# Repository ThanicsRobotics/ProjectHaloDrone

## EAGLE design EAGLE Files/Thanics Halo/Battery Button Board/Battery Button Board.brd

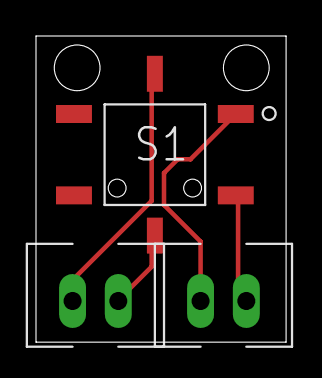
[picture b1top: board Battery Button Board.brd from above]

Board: 2 copper layers, 13.9 x 17.0 mm, 3 parts (0 on the bottom side), 4 nets.

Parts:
D1: XH_CONNECTOR
S1: SWITCH_CONNECTOR; XH_CONNECTOR
U$1: LED_TACT_SWITCH

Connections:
GND: D1.2, U$1.5
unnamed: D1.1, U$1.6
unnamed: S1.1, U$1.1
unnamed: S1.2, U$1.3

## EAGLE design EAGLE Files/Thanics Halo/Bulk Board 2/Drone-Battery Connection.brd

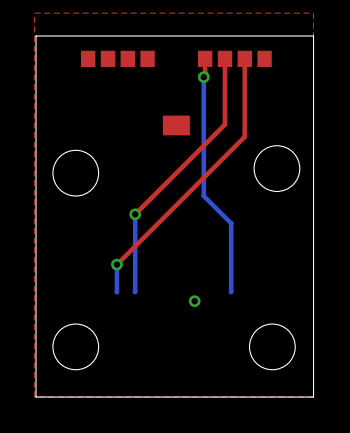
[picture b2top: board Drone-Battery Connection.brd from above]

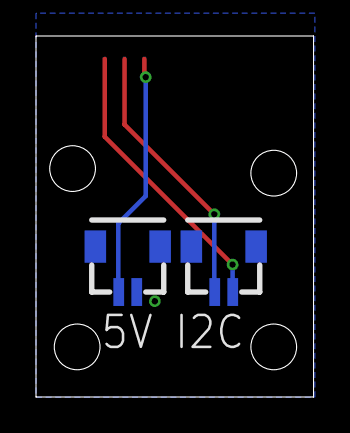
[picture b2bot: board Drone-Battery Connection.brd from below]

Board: 2 copper layers, 15.4 x 20.1 mm, 3 parts (2 on the bottom side), 4 nets.

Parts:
U$1: SPRING_BTB_8POS_MALE
U$2, U$3: JST_SH_2POS

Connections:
+5V: U$1.5, U$3.1
GND: U$1.8, U$3.2
SCL: U$1.7, U$2.2
SDA: U$1.6, U$2.1

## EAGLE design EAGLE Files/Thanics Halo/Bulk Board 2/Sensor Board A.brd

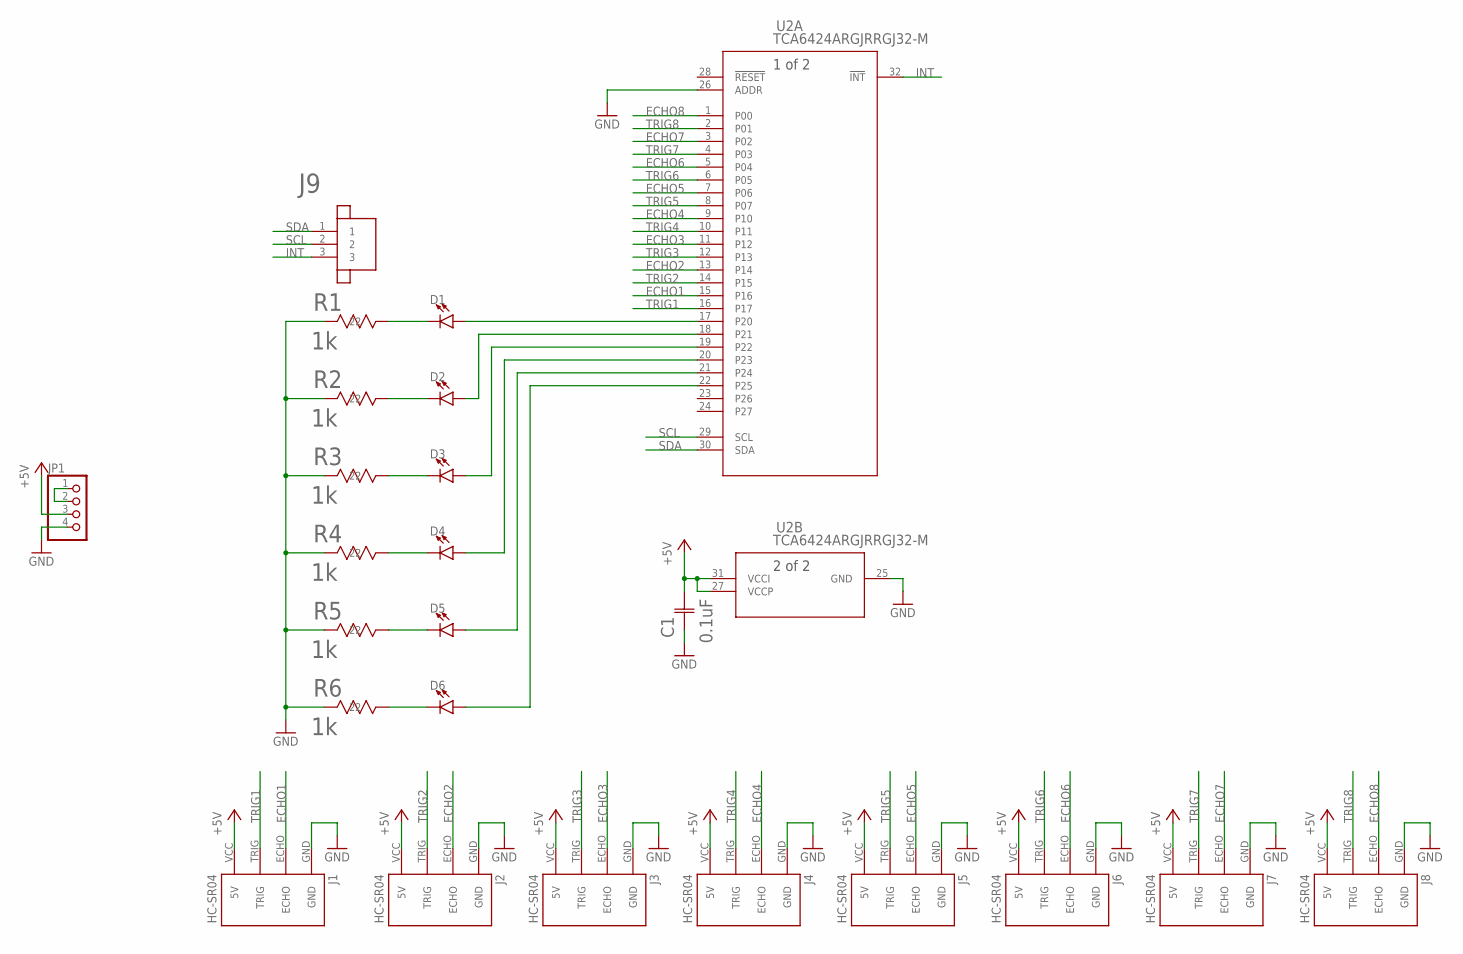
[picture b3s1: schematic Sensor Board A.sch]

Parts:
C1: 0.1uF; 0805
D1, D2, D3, D4, D5, D6: LED0603; LED-0603
J1, J2, J3, J4, J5, J6, J7, J8: HC-SR04; HC-SR04_FOOTPRINT
J9: JST_SH_3POS
JP1: PINHD-1X4; 1X04
R1, R2, R3, R4, R5, R6: 1k; RC0603N-M
U2: TCA6424ARGJRRGJ32-M; RGJ32-M

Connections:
+5V: C1.2, J1.VCC (5V), J2.VCC (5V), J3.VCC (5V), J4.VCC (5V), J5.VCC (5V), J6.VCC (5V), J7.VCC (5V), J8.VCC (5V), JP1.3, U2.27 (VCCP), U2.31 (VCCI)
ECHO1: J1.ECHO, U2.15 (P16)
ECHO2: J2.ECHO, U2.13 (P14)
ECHO3: J3.ECHO, U2.11 (P12)
ECHO4: J4.ECHO, U2.9 (P10)
ECHO5: J5.ECHO, U2.7 (P06)
ECHO6: J6.ECHO, U2.5 (P04)
ECHO7: J7.ECHO, U2.3 (P02)
ECHO8: J8.ECHO, U2.1 (P00)
GND: C1.1, J1.GND, J2.GND, J3.GND, J4.GND, J5.GND, J6.GND, J7.GND, J8.GND, JP1.4, R1.2 (22), R2.2 (22), R3.2 (22), R4.2 (22), R5.2 (22), R6.2 (22), U2.25 (GND), U2.26 (ADDR)
INT: J9.3, U2.32 (!INT)
unnamed: JP1.1, JP1.2
unnamed: D1.A, U2.17 (P20)
unnamed: D2.A, U2.18 (P21)
unnamed: D3.A, U2.19 (P22)
unnamed: D4.A, U2.20 (P23)
unnamed: D5.A, U2.21 (P24)
unnamed: D6.A, U2.22 (P25)
unnamed: D6.C, R6.1 (11)
unnamed: D5.C, R5.1 (11)
unnamed: D4.C, R4.1 (11)
unnamed: D3.C, R3.1 (11)
unnamed: D2.C, R2.1 (11)
unnamed: D1.C, R1.1 (11)
SCL: J9.2, U2.29 (SCL)
SDA: J9.1, U2.30 (SDA)
TRIG1: J1.TRIG, U2.16 (P17)
TRIG2: J2.TRIG, U2.14 (P15)
TRIG3: J3.TRIG, U2.12 (P13)
TRIG4: J4.TRIG, U2.10 (P11)
TRIG5: J5.TRIG, U2.8 (P07)
TRIG6: J6.TRIG, U2.6 (P05)
TRIG7: J7.TRIG, U2.4 (P03)
TRIG8: J8.TRIG, U2.2 (P01)

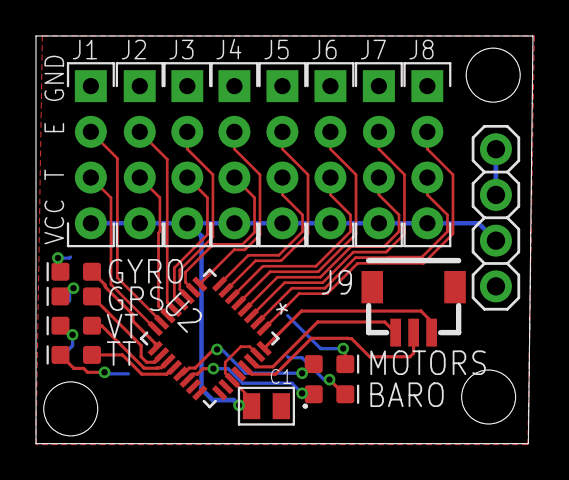
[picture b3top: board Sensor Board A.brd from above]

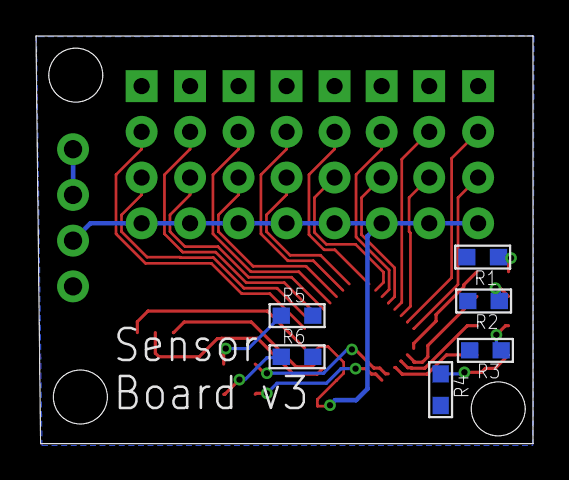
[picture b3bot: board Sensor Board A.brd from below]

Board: 2 copper layers, 27.6 x 22.6 mm, 24 parts (6 on the bottom side), 34 nets.

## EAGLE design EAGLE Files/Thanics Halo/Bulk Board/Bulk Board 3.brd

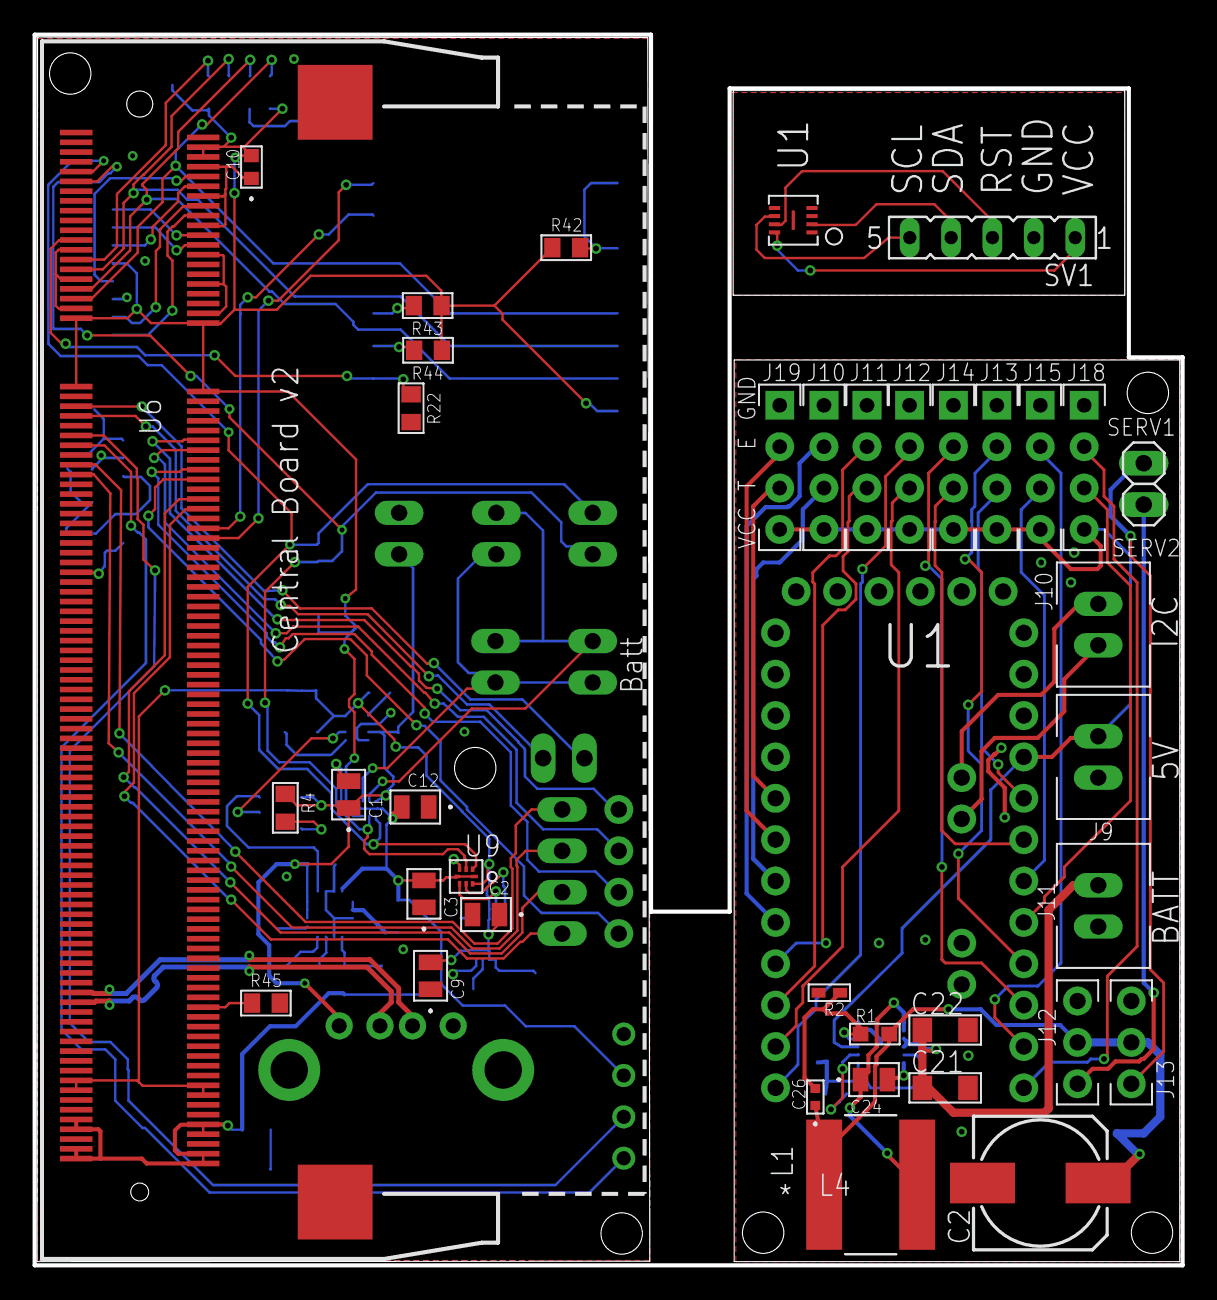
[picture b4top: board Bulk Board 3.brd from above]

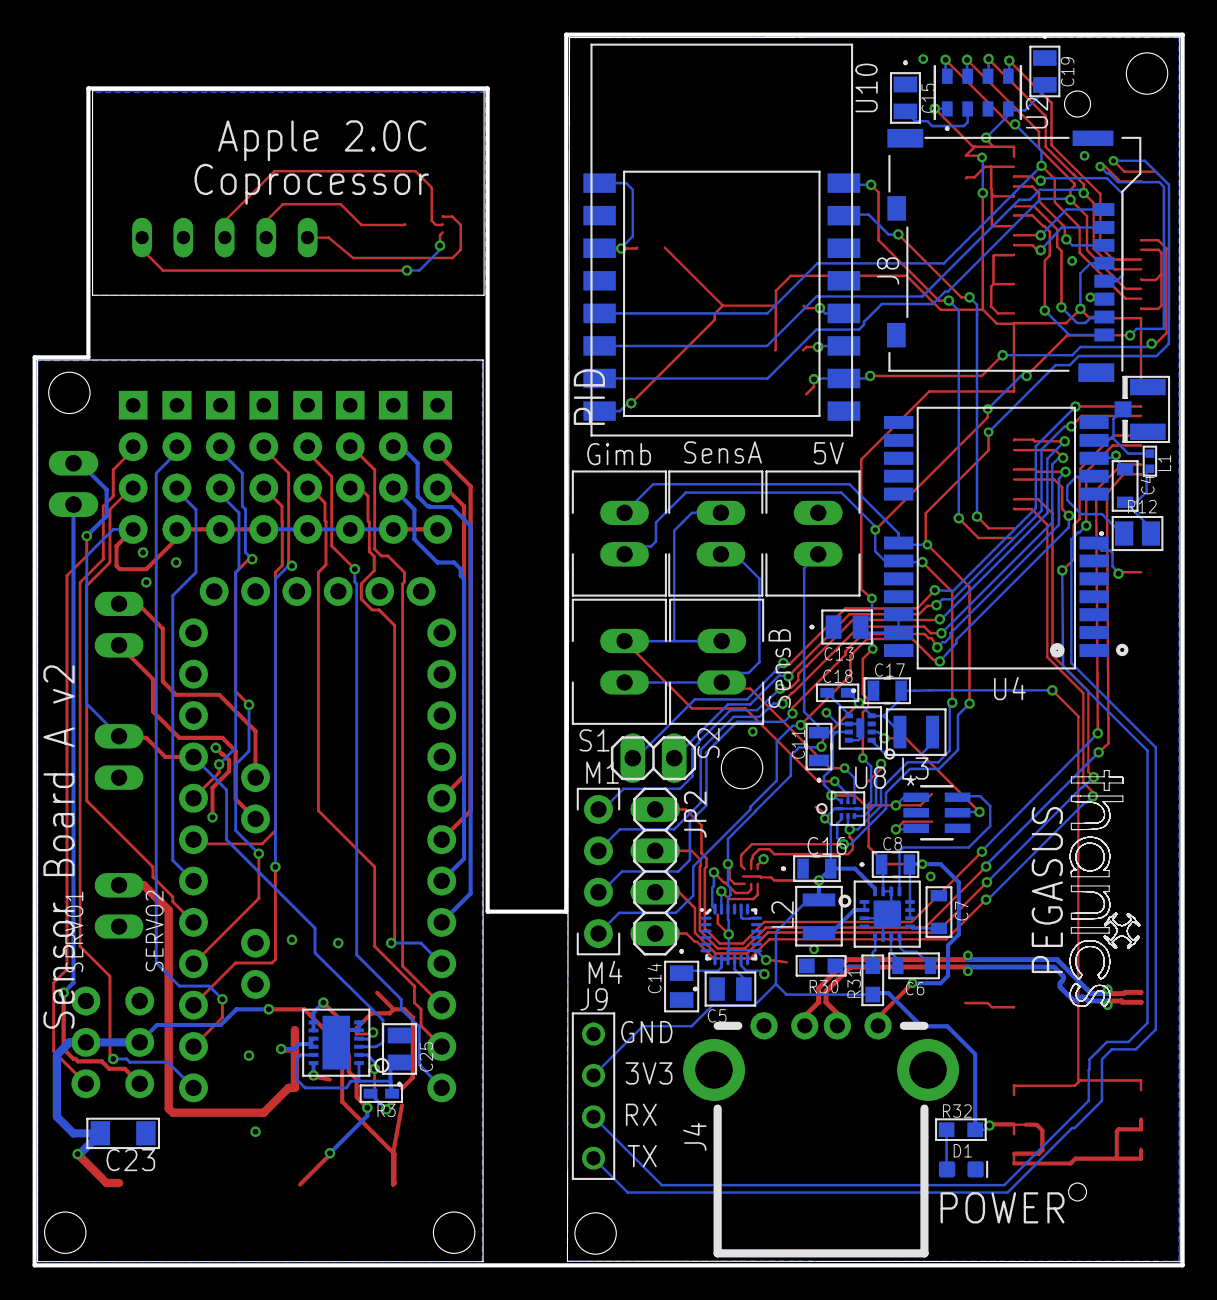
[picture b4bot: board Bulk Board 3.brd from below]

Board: 2 copper layers, 70.5 x 75.6 mm, 84 parts (45 on the bottom side), 91 nets.

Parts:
C1, C2, C3, C5, C9, C12, C13, C14, C24, C25: 0.1uF; 0805
C4: 10 nF; 0603_CAPACITOR
C6, C7: 10nF; 0603_CAPACITOR
C8, C11, C17: 10uF; G-21
C10: 2.2uF; G-188-M
C15, C19: 1uF; YAG_CC0805
C16: 22uF; G-21
C18: 560pF; CC0402N-M
C20: 100uF; 0810_POLCAP
C21, C22, C23: 10uF; 1206_MLCC
C26: 16pF; G-155-M
D1: GREEN; LED-0603
J1, J16: POWER_CONNECTOR; XH_CONNECTOR
J2, J3, J6, J7, J17: I2C_CONNECTOR; XH_CONNECTOR
J4: USB_A_RECEPT
J5: U.FL
J8: MICROSD
J9: 4_PIN_TELE_CONNECTOR
J10, J11, J12, J13, J14, J15, J18, J19: HC-SR04; HC-SR04_FOOTPRINT
J20, J21: SERVO_CONNECTOR
J22: GIMBAL_POWER_CONNECTOR; XH_CONNECTOR
JP1, JP3: 1X02
JP2: 1X04
L1: 27 nH; 0402_INDUCTOR
L2, L3: 470nH; 470NH_INDUCTOR
L4: 3.3uH; IND_BOURNS_SRN8040
R1, R31: 499k; RC0603N-M
R2, R3: 95.3k; RC0402N-M
R4, R22, R42, R43, R44, R45: 10k; RC0805N
R12: 10; STA_RNCP0805-M
R30: 160k; RC0603N-M
R32: 20R; RC0603N-M
SV1: FE05-1
U1: QFN40P300X300X105-25N
U2: LGA8-M
U3: LM3880MF-1AA/NOPBMF06A-M; MF06A-M
U4: NEO-M8
U5: TPS6209; VQFN16
U6: COMPUTE_MODULE; SO-DIMM
U7: MIC23050; MLF(ML)_8PIN
U8, U9: 8-UMLP
U10: ESP-12
U11: PRO-MINI-2
U$1: 12LD4X3DFN
U$2: APPLE_2.0C_COPROCESSOR; PG-USON-8-1
U$12: 4_PIN_CONNECTOR

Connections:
1.8V: C2.1, C9.2, C14.1, C17.2, C18.2, L3.P$2, U1.8, U1.9, U1.13, U1.22, U6.183, U6.184, U6.185, U6.186, U7.4, U9.8
+3V3: C3.2, C10.2, C12.2, C13.2, C16.2, C19.2, J8.4, J9.3, L2.P$2, R31.1, R32.2, R42.1, R43.1, R44.1, U2.1, U2.4, U4.22, U4.23, U5.16, U6.4, U6.6, U6.39, U6.40, U6.41, U6.42, U6.191, U6.192, U6.193, U6.194, U6.197, U6.198, U6.199, U6.200, U8.1, U8.5, U9.1, U9.5, U10.8
+5V: C1.1, C8.2, C11.2, J1.1, J4.1, R4.1, U3.1, U5.10, U5.11, U5.12, U7.7, U8.8
+5V1: J10.VCC, J11.VCC, J12.VCC, J13.VCC, J14.VCC, J15.VCC, J16.1, J18.VCC, J19.VCC, U11.VCC, U$1.3
ECHO1: J19.ECHO, U11.D3
ECHO2: J10.ECHO, U11.D5
ECHO3: J11.ECHO, U11.D7
ECHO4: J12.ECHO, U11.D9
ECHO5: J13.ECHO, U11.D13
ECHO6: J14.ECHO, U11.D12
ECHO7: J15.ECHO, U11.D11
ECHO8: J18.ECHO, U11.D10
GND: C1.2, C2.2, C3.1, C4.1, C5.1, C7.1, C8.1, C9.1, C10.1, C11.1, C12.1, C13.1, C14.2, C15.1, C16.1, C17.1, C19.1, D1.C, J1.2, J4.4, J4.5, J4.6, J5.P$1, J5.P$2, J8.6, J8.9, J8.10, J8.11, J8.12, J8.13, J9.4, R22.2, R30.2, R45.2, U1.11, U1.18, U1.20, U2.3, U3.2, U4.7, U4.10, U4.12, U4.13, U4.24, U5.3, U5.6, U5.14, U5.15, U5.17, U6.1, U6.7, U6.8, U6.13, U6.14, U6.19, U6.20, U6.25, U6.26, U6.31, U6.32, U6.37, U6.38, U6.43, U6.44, U6.49, U6.50, U6.55, U6.56, U6.61, U6.62, U6.67, U6.68, U6.73, U6.74, U6.79, U6.80, U6.85, U6.86, U6.91, U6.92, U6.97, U6.98, U6.103, U6.104, U6.109, U6.110, U6.115, U6.116, U6.121, U6.122, U6.127, U6.133, U6.134, U6.139, U6.140, U6.145, U6.146, U6.151, U6.152, U6.157, U6.163, U6.164, U6.169, U6.170, U6.181, U6.182, U6.187, U6.188, U6.195, U6.196, U6.G1, U6.G2, U7.6, U7.8, U7.EP, U8.4, U9.4, U10.9
GND1: C20.-, C21.P$2, C22.P$2, C23.P$1, C25.2, J10.GND, J11.GND, J12.GND, J13.GND, J14.GND, J15.GND, J16.2, J18.GND, J19.GND, J20.3, J21.3, J22.2, R2.2, U11.GND, U11.GND1, U$1.5, U$1.6, U$1.EP
GND2: SV1.2, U$2.1, U$2.9
I2C_SCL: J7.1, U4.19, U6.11, U8.3, U9.3
I2C_SCL_1V8: U1.23, U9.6
I2C_SCL_5V: J2.1, J3.1, J6.1, U8.6
I2C_SDA: J7.2, U4.18, U6.9, U8.2, U9.2
I2C_SDA_1V8: U1.24, U9.7
I2C_SDA_5V: J2.2, J3.2, J6.2, U8.7
LED1: JP2.1, U6.57
LED2: JP2.2, U6.59
LED3: JP2.3, U6.64
LED4: JP2.4, U6.66
MOTOR1: U6.52, U$12.1
MOTOR2: U6.54, U$12.2
MOTOR3: U6.58, U$12.3
MOTOR4: U6.60, U$12.4
unnamed: J5.P$3, L1.P$1, U4.11
unnamed: C6.2, U5.7
unnamed: C6.1, U5.8
unnamed: D1.A, R32.1
unnamed: U3.6, U5.13
unnamed: U3.5, U7.2
unnamed: C26.2, R1.1, R2.1, U$1.4
unnamed: C24.2, U$1.12
unnamed: C24.1, L4.2, U$1.7, U$1.8
unnamed: R3.2, U$1.2
unnamed: C5.2, U1.10
unnamed: C15.2, U2.2
unnamed: R12.1, U4.9
unnamed: C4.2, L1.P$2, R12.2
unnamed: C7.2, U5.9
unnamed: L2.P$1, U5.1, U5.2
unnamed: L3.P$1, U7.1
unnamed: R42.2, U10.1, U10.3
unnamed: R43.2, U10.12
unnamed: R30.1, R31.2, U5.5
unnamed: C18.1, U7.5
unnamed: R44.2, U10.11
unnamed: R45.1, U6.168
POWER_SEQ_EN: R4.2, U3.3
RST: SV1.3, U$2.7
SCL: J17.1, U11.A5
SCL1: SV1.5, U$2.6
SDA: J17.2, U11.A4
SDA1: SV1.4, U$2.2
SDX_CLK: J8.5, U6.10
SDX_CMD: J8.3, U6.12
SDX_D0: J8.7, U6.16
SDX_D1: J8.8, U6.18
SDX_D2: J8.1, U6.22
SDX_D3: J8.2, U6.24
SERVO1: JP1.1, U6.45
SERVO2: JP1.2, U6.47
SERVO3: J21.1, JP3.2
SERVO4: J20.1, JP3.1
SPI_CS0: U2.5, U6.27
SPI_CS1: R22.1, U6.23, U10.10
SPI_MISO: U2.6, U6.29, U10.6
SPI_MOSI: U2.7, U6.33, U10.7
SPI_SCLK: U2.8, U6.35, U10.5
TRIG1: J19.TRIG, U11.D2
TRIG2: J10.TRIG, U11.D4
TRIG3: J11.TRIG, U11.D6
TRIG4: J12.TRIG, U11.D8
TRIG5: J13.TRIG, U11.A0
TRIG6: J14.TRIG, U11.A1
TRIG7: J15.TRIG, U11.A2
TRIG8: J18.TRIG, U11.A3
UART2_RX: U6.72, U10.16
UART2_TX: U6.70, U10.15
UART_RX: J9.1, U6.53
UART_TX: J9.2, U6.51
USB_D_N: J4.2, U6.167
USB_D_P: J4.3, U6.165
VCC: SV1.1, U$2.8
VDD: C25.1, R3.1, U$1.1, U$1.11
VOUT: C20.+, C23.P$2, C26.1, J20.2, J21.2, L4.1, R1.2
V_BATT: C21.P$1, C22.P$1, J22.1, U$1.9, U$1.10

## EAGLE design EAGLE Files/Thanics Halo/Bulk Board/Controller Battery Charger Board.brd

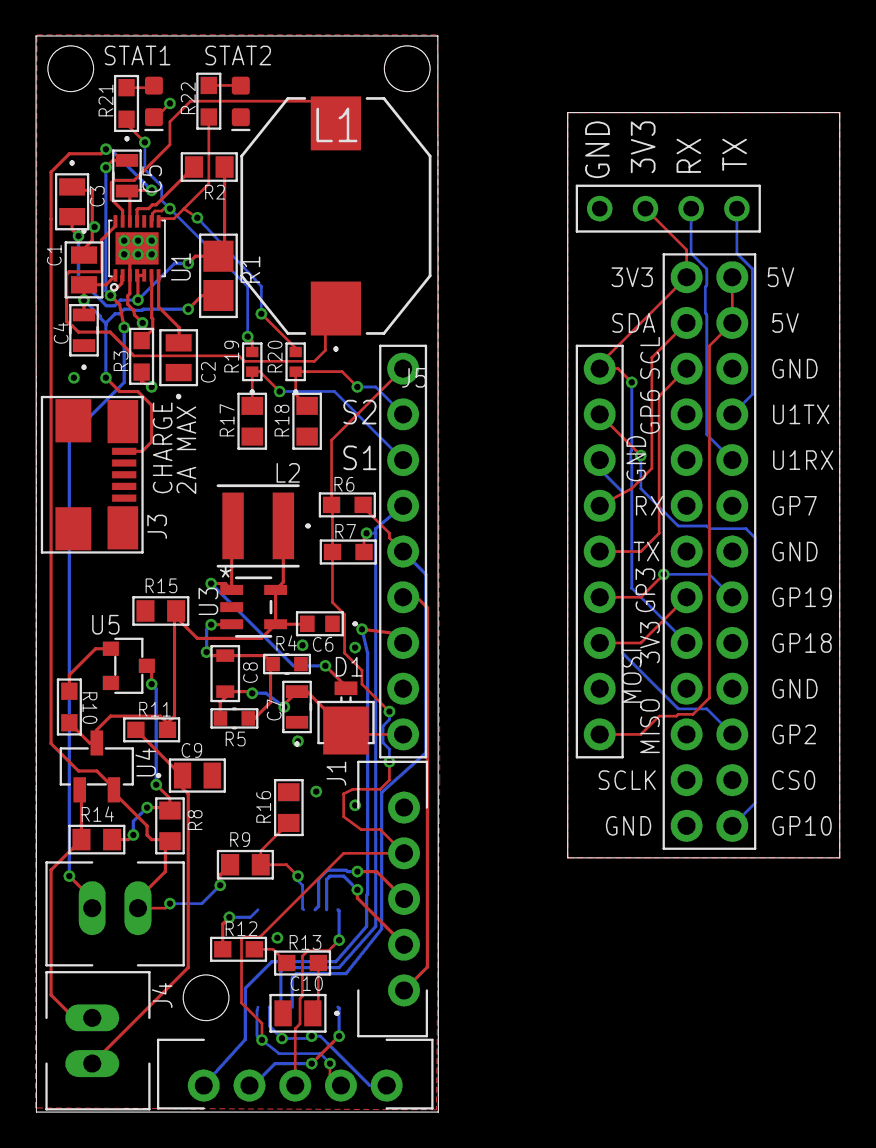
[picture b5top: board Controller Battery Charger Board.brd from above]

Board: 2 copper layers, 22.4 x 59.8 mm, 51 parts (1 on the bottom side), 48 nets.

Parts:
C1, C2, C10: 0.1uF; 0805
C3, C9: 1uF; YAG_CC0805
C4, C7: 10uF; G-21
C5: 22uF; G-21
C6: 2.2uF; G-188-M
C8: 470pF; 0603_CAPACITOR
D1: UPS5817_SCHOTTKY_DIODE; UPS5817_DIODE
D2: GREEN; LED-0603
D3: RED; LED-0603
J1, J2: JOYSTICK; JST-XH_5POS
J3: USB_MICRO_B_SMT
J4: 2_PIN_CONNECTOR; XH_CONNECTOR
J5, J7: RPI-AUX_BOARD_CONNECTOR; 9_PIN_CONNECTOR
J6: POWER_CONNECTOR; XH_CONNECTOR
L1: 4.7 uH; IND_BOURNS_SRR1005
L2: 10uH; IND_TAIYO_NR4018
R1: 100; 1206
R2, R8, R9, R14, R15, R16, R17, R18: 10k; RC0805N
R3, R10: 100k; RC0603N-M
R4: 13.3k; RC0603N
R5: 43k; RC0603N
R6, R7, R12, R13, R21, R22: 1k; RC0603N-M
R11: 1M; RC0603N-M
R19, R20: 5k; 0402
U1: AAT3620_BATT_CHARGER; AAT3620_TDFN
U2: 8 CH; 21-0055H_16-M
U3: LM27313XMF/NOPB; MF05A
U4: DMP3030SN_MOSFET; SC59_MOSFET
U5: SOT-23_(TO-236AB)
U$1: ORANGE_PI_ADAPTER1; ORANGE_PI_ADAPTER
U$3: 4_PIN_TELE_CONNECTOR

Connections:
+3V3: J1.2, J2.2, J5.9, R6.1, R7.1, U2.16
+5V: C7.2, C8.2, D1.C, J5.1, R5.2
GND: C1.1, C2.1, C3.1, C4.1, C6.1, C7.1, C9.2, C10.2, D2.C, D3.C, J1.1, J2.1, J3.5, J3.P$1, J3.P$2, J3.P$3, J3.P$4, J5.2, R3.1, R4.2, R15.1, R16.2, R17.1, R18.1, U1.3, U1.EP, U2.15, U3.2, U5.S
GNDA: J7.2, U$1.P$6, U$1.P$9, U$1.P$14, U$1.P$20, U$1.P$25, U$3.4
unnamed: J4.1, R14.1, U4.G
unnamed: C2.2, U1.7
unnamed: R3.2, U1.6
unnamed: L1.2, U1.13
unnamed: L1.1, U1.14
unnamed: C3.2, R1.1, R2.1, U1.4, U1.5
unnamed: C5.2, J6.1, R8.2, R9.1, U1.12, U4.S
unnamed: C8.1, R4.1, R5.1, U3.3
unnamed: J5.7, R17.2, R19.1
unnamed: J5.8, R18.2, R20.1
unnamed: R2.2, U1.11
unnamed: D1.A, L2.2, U3.1
unnamed: J7.1, U$1.P$2, U$1.P$4
unnamed: J5.6, R7.2, U2.14
unnamed: J1.5, J5.4
unnamed: R12.1, U2.1
unnamed: J1.3, U2.6
unnamed: J1.4, U2.7
unnamed: J2.3, U2.8
unnamed: J2.4, U2.9
unnamed: J5.5, R6.2, U2.13
unnamed: J2.5, J5.3
unnamed: C6.2, L2.1, R10.2, R11.2, R15.2, U3.4, U3.5, U4.D
unnamed: R12.2, R13.1
unnamed: R10.1, U5.G
unnamed: C9.1, J4.2, R11.1
unnamed: R8.1, R14.2, U5.D
unnamed: C10.1, R13.2
unnamed: J7.8, U$1.P$26
unnamed: J7.7, U$1.P$22
unnamed: J7.6, U$1.P$3
unnamed: J7.5, U$1.P$5
unnamed: C5.1, J6.2, U1.2
unnamed: J7.4, U$1.P$16
unnamed: J7.3, U$1.P$15
unnamed: U$1.P$8, U$3.1
unnamed: U$1.P$10, U$3.2
unnamed: R9.2, R16.1, U2.5
unnamed: R20.2, R22.1, U1.8
unnamed: J7.9, U$1.P$1, U$1.P$17, U$3.3
unnamed: D2.A, R21.2
unnamed: D3.A, R22.2
unnamed: R19.2, R21.1, U1.9
USB_5V: C1.2, C4.2, J3.1, R1.2, U1.1

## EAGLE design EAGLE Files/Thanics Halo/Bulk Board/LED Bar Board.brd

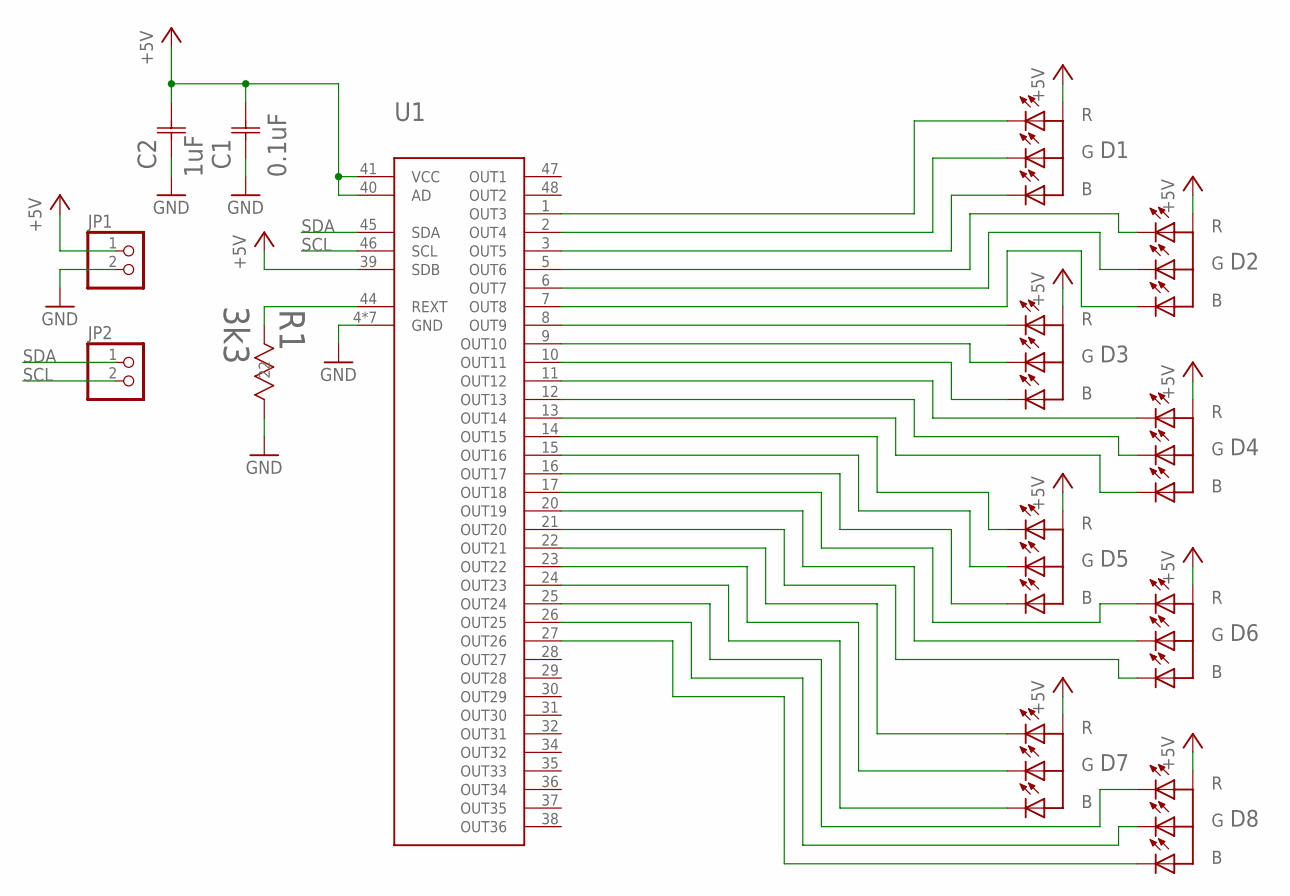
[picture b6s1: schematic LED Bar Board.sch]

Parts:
C1: 0.1uF; 0805
C2: 1uF; YAG_CC0805
D1, D2, D3, D4, D5, D6, D7, D8: ASMB-MTB0-0A3A2; ASMB-MTB0_LED
JP1, JP2: PINHD-1X2; 1X02
R1: 3k3; RC1206N-M
U1: IS31FL3236; TQFP-48

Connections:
+5V: C1.2, C2.2 (22), D1.1 (A), D2.1 (A), D3.1 (A), D4.1 (A), D5.1 (A), D6.1 (A), D7.1 (A), D8.1 (A), JP1.1, U1.39 (SDB), U1.40 (AD), U1.41 (VCC)
GND: C1.1, C2.1 (11), JP1.2, R1.1 (11), U1.4 (GND), U1.18 (GND), U1.19 (GND), U1.33 (GND), U1.42 (GND), U1.43 (GND), U1.EP (GND)
unnamed: D1.4 (R), U1.1 (OUT3)
unnamed: D1.3 (G), U1.2 (OUT4)
unnamed: D2.3 (G), U1.6 (OUT7)
unnamed: D1.2 (B), U1.3 (OUT5)
unnamed: D2.4 (R), U1.5 (OUT6)
unnamed: R1.2 (22), U1.44 (REXT)
unnamed: D3.4 (R), U1.8 (OUT9)
unnamed: D3.3 (G), U1.9 (OUT10)
unnamed: D3.2 (B), U1.10 (OUT11)
unnamed: D4.4 (R), U1.11 (OUT12)
unnamed: D4.3 (G), U1.12 (OUT13)
unnamed: D4.2 (B), U1.13 (OUT14)
unnamed: D5.4 (R), U1.14 (OUT15)
unnamed: D5.3 (G), U1.15 (OUT16)
unnamed: D5.2 (B), U1.16 (OUT17)
unnamed: D6.4 (R), U1.17 (OUT18)
unnamed: D6.3 (G), U1.20 (OUT19)
unnamed: D6.2 (B), U1.21 (OUT20)
unnamed: D7.4 (R), U1.22 (OUT21)
unnamed: D7.3 (G), U1.23 (OUT22)
unnamed: D7.2 (B), U1.24 (OUT23)
unnamed: D8.4 (R), U1.25 (OUT24)
unnamed: D8.3 (G), U1.26 (OUT25)
unnamed: D8.2 (B), U1.27 (OUT26)
unnamed: D2.2 (B), U1.7 (OUT8)
SCL: JP2.2, U1.46 (SCL)
SDA: JP2.1, U1.45 (SDA)

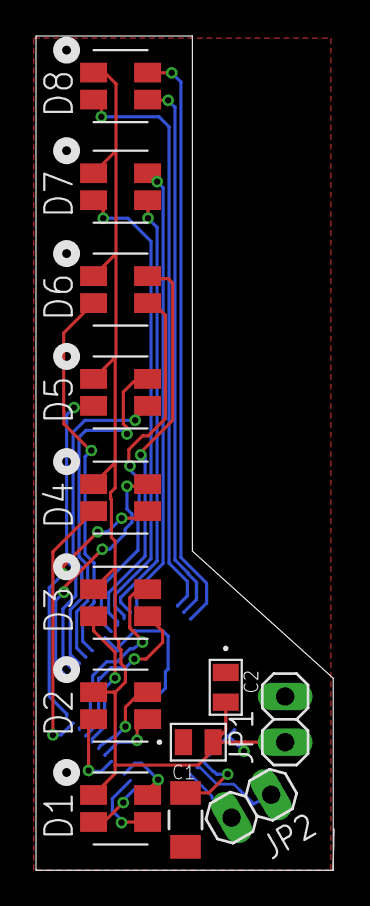
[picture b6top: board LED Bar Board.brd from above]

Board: 2 copper layers, 16.5 x 46.3 mm, 14 parts (1 on the bottom side), 29 nets.

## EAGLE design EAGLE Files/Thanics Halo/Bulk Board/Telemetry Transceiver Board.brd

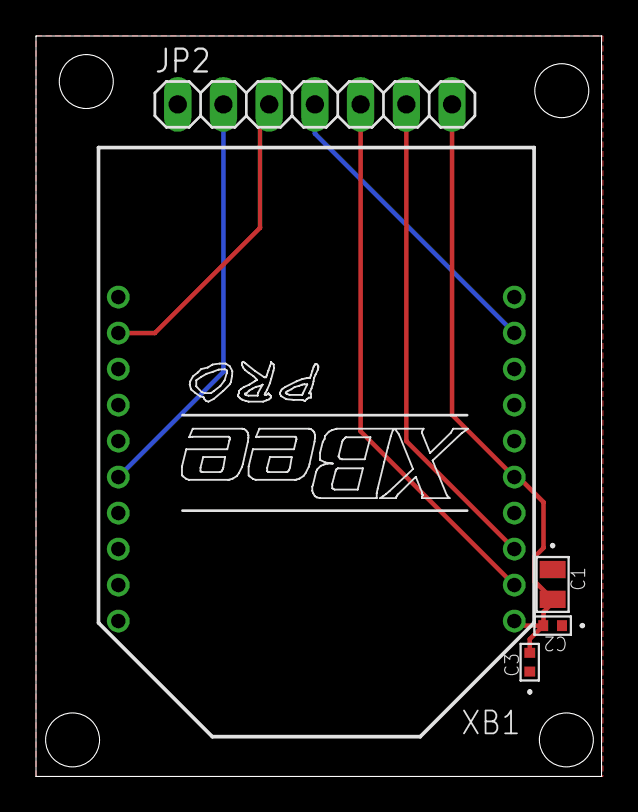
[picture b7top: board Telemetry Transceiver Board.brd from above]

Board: 2 copper layers, 31.4 x 41.1 mm, 5 parts (0 on the bottom side), 7 nets.

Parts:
C1: 1uF; YAG_CC0805
C2, C3: 16pF; G-155-M
JP2: 1X07
XB1: XBEE-PRO

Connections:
!CTS: JP2.3, XB1.12
!DTR: JP2.4, XB1.9
!RTS: JP2.2, XB1.16
+3V3: C1.2, C2.2, C3.2, JP2.7, XB1.1, XB1.5
GND: C1.1, C2.1, C3.1, JP2.1, XB1.10, XB1.14
RX: JP2.6, XB1.3
TX: JP2.5, XB1.2

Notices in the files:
parts and their libraries:
SparkFun-LED: Licensing: Creative Commons ShareAlike 4.0 International - https://creativecommons.org/licenses/by-sa/4.0
COPYRIGHT: Copyright C 2015 Accelerated Designs. All rights reserved
